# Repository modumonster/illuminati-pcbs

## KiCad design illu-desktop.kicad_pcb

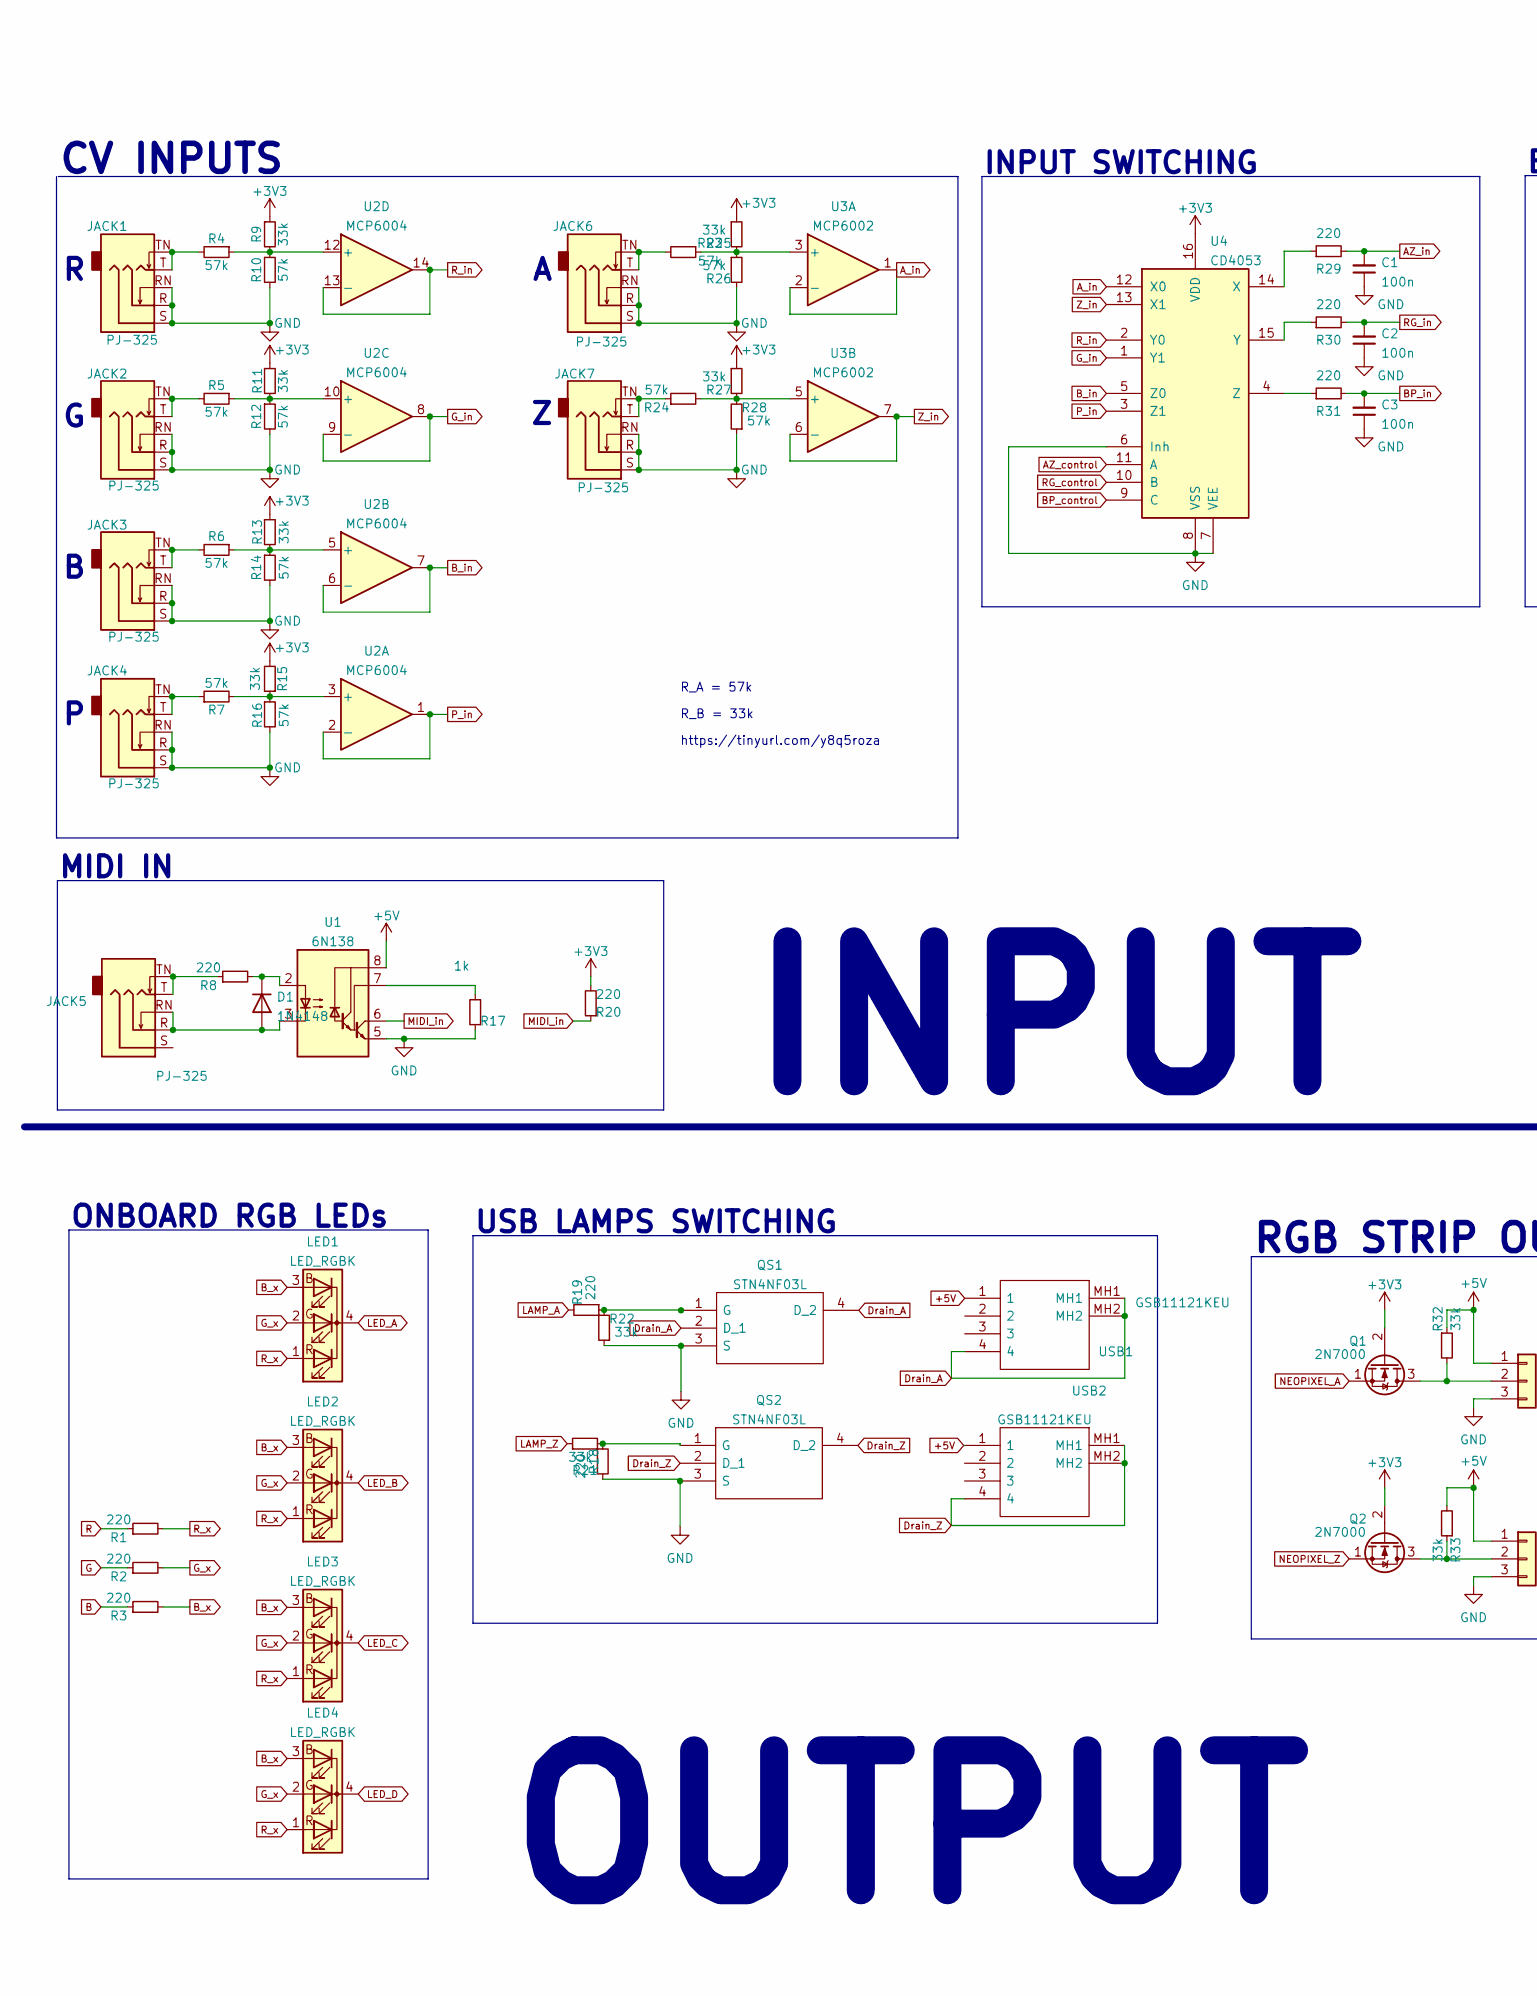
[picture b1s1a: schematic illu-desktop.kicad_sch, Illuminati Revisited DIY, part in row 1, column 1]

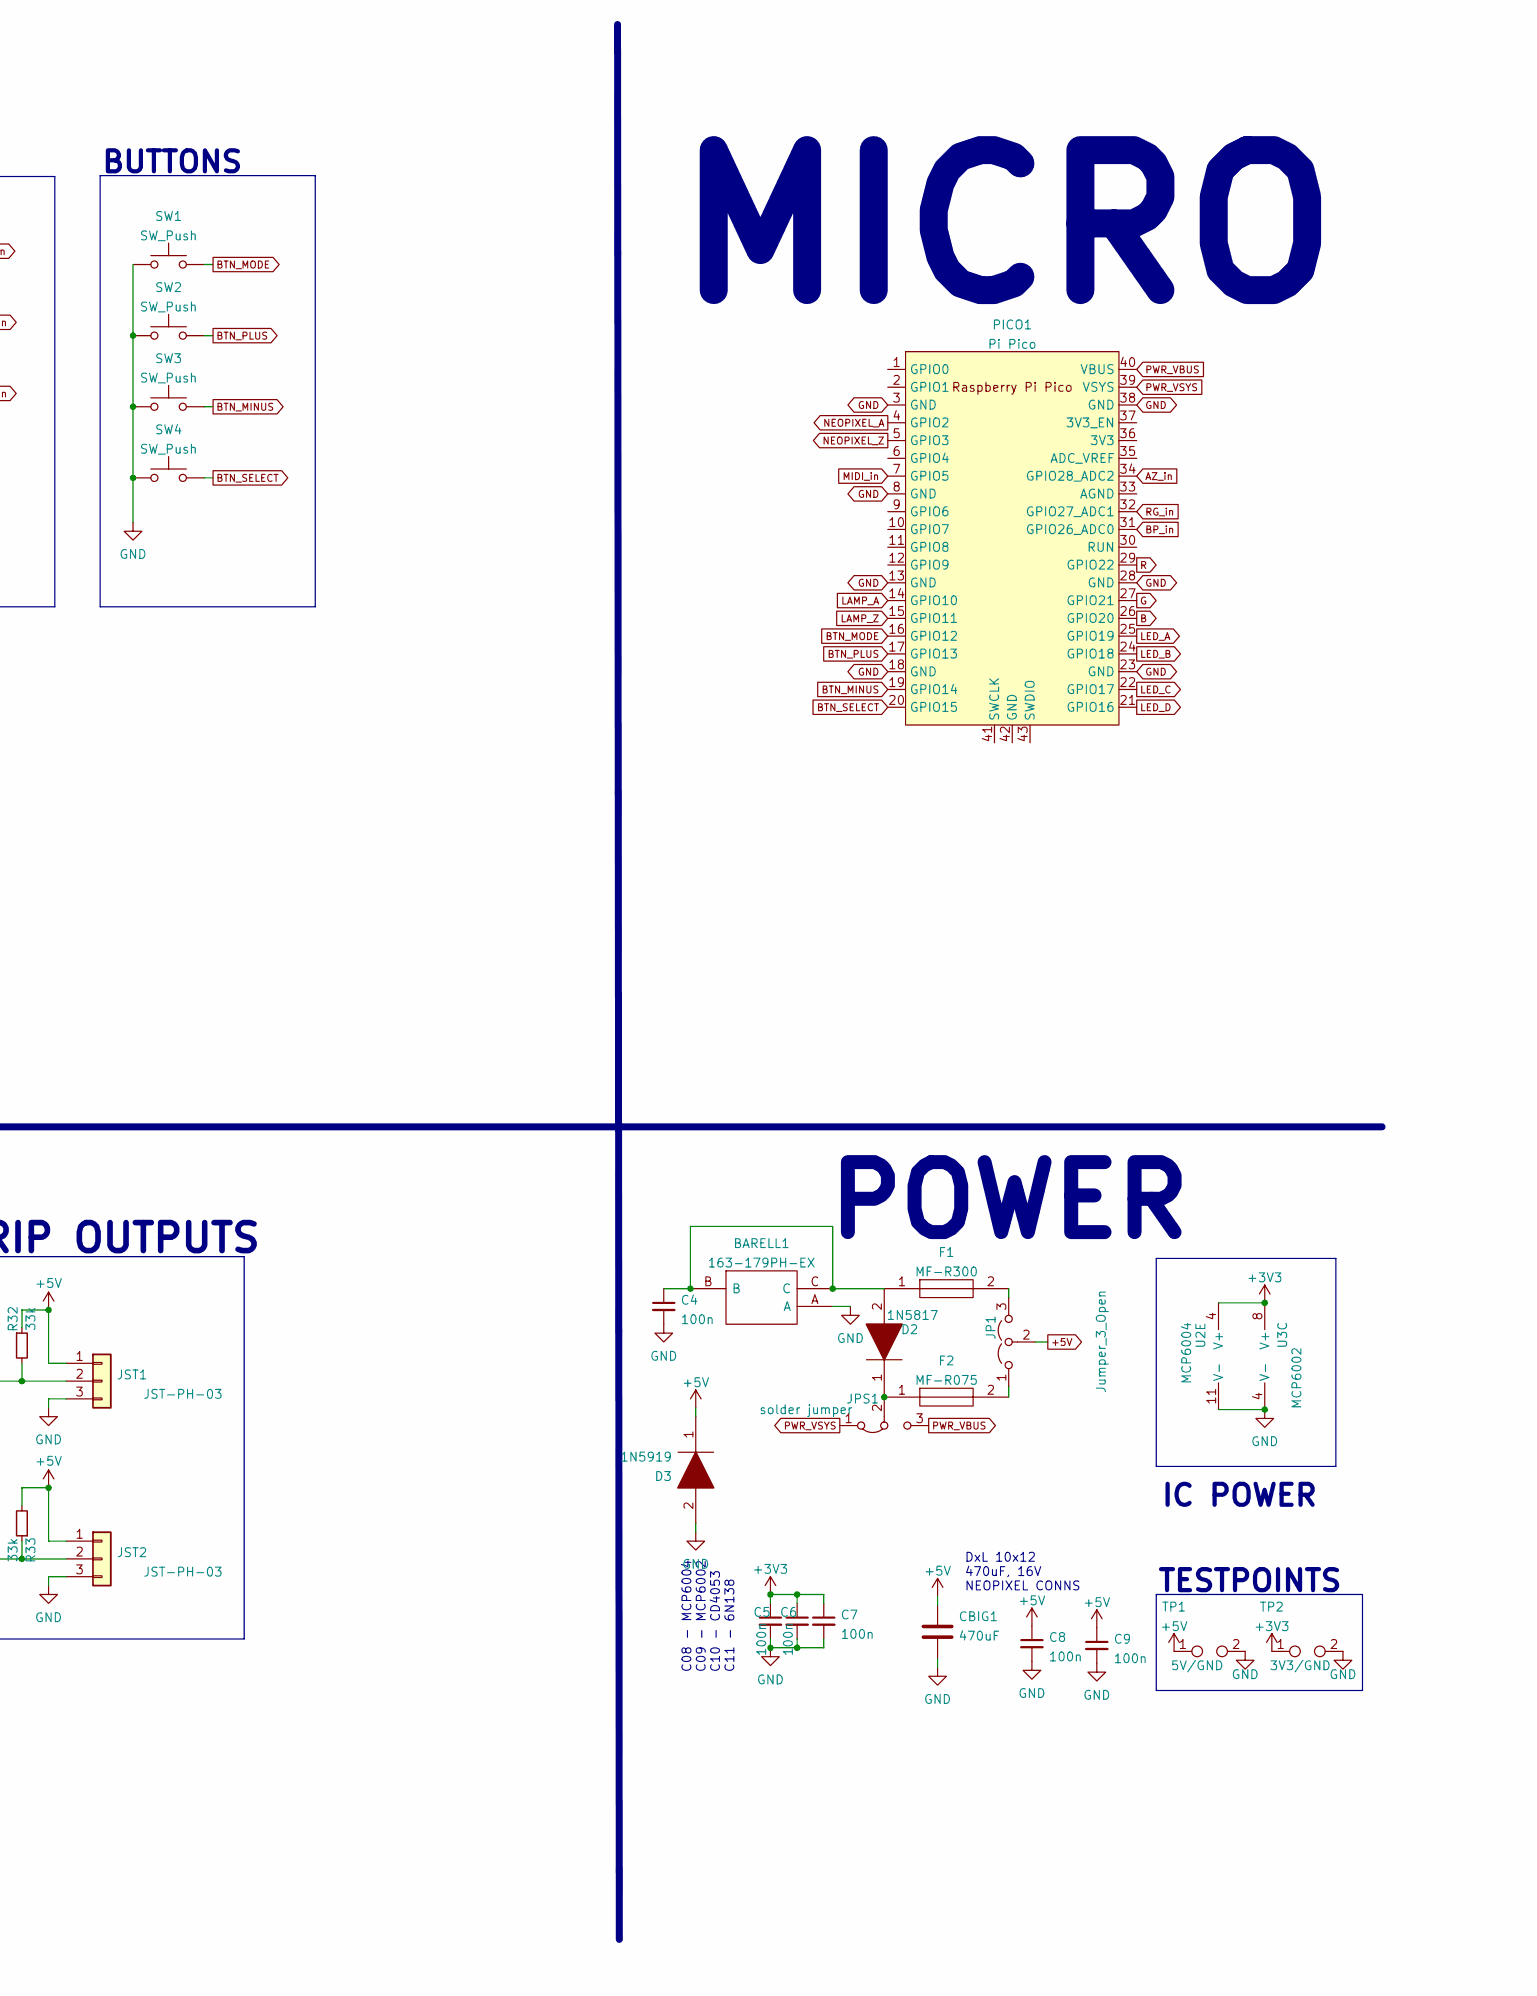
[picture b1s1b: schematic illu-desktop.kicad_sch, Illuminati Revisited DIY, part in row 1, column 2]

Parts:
BARELL1: 163-179PH-EX; BarellJack; Mouser Part Number 163-179PH-EX
C1, C2, C3, C4, C5, C6, C7, C8, C9: 100n; C_Rect_L7.0mm_W2.5mm_P5.00mm
CBIG1: 470uF; CP_Radial_D10.0mm_P5.00mm
D1: 1N4148; D_DO-35_SOD27_P7.62mm_Horizontal
D2: 1N5817; D_DO-41_SOD81_P7.62mm_Horizontal; Mouser Part Number 863-1N5817RLG
D3: 1N5919; D_DO-41_SOD81_P7.62mm_Horizontal; Mouser Part Number 863-1N5919BG
F1: MF-R300; MFR300; Mouser Part Number 652-MFR300
F2: MF-R075; MFR075; Mouser Part Number 652-MFR075
JACK1, JACK2, JACK3, JACK4, JACK5, JACK6, JACK7: PJ-325; PJ-325C5
JP1: Jumper_3_Open; PinHeader_1x03_P2.54mm_Horizontal
JPS1: solder jumper; SolderJumper-3_P1.3mm_Bridged12_RoundedPad1.0x1.5mm
JST1, JST2: JST-PH-03; JST_PH_S3B-PH-K_1x03_P2.00mm_Horizontal
LED1, LED2, LED3, LED4: LED_RGBK; LED_D5.0mm-4_RGB
PICO1: Pi Pico; RPi_Pico_TH
Q1, Q2: 2N7000; TO-92_Inline
QS1, QS2: STN4NF03L; SOT233P700X180-4N; Mouser Part Number 511-STN4NF03L
R1, R2, R3: 220; R_Axial_DIN0207_L6.3mm_D2.5mm_P7.62mm_Horizontal
R4, R5, R6, R7, R10, R12, R14, R16, R23, R24, R26, R28: 57k; R_Axial_DIN0207_L6.3mm_D2.5mm_P2.54mm_Vertical
R8, R18, R19, R20, R29, R30, R31: 220; R_Axial_DIN0207_L6.3mm_D2.5mm_P2.54mm_Vertical
R9, R11, R13, R15, R21, R22, R25, R27, R32, R33: 33k; R_Axial_DIN0207_L6.3mm_D2.5mm_P2.54mm_Vertical
R17: 1k; R_Axial_DIN0207_L6.3mm_D2.5mm_P2.54mm_Vertical
SW1, SW2, SW3, SW4: SW_Push; SW_PUSH_6mm_H17mm
TP1: 5V/GND; TestPoint_2Pads_Pitch2.54mm_Drill0.8mm
TP2: 3V3/GND; TestPoint_2Pads_Pitch2.54mm_Drill0.8mm
U1: 6N138; DIP-8_W7.62mm
U2: MCP6004; DIP-14_W7.62mm
U3: MCP6002; DIP-8_W7.62mm
U4: CD4053; DIP-16_W7.62mm
USB1, USB2: GSB11121KEU; Mouser Part Number 523-GSB11121KEU

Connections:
+3V3: C5.1, C6.1, C7.1, Q1.2 (G), Q2.2 (G), R9.1, R11.1, R13.1, R15.2, R20.2, R25.1, R27.1, TP2.1, U2.4 (V+), U3.8 (V+), U4.16 (VDD)
+5V: C8.1, C9.1, CBIG1.1, D3.1, JP1.2 (C), JST1.1, JST2.1, R32.1, R33.2, TP1.1, U1.8 (VCC), USB1.1, USB2.1
AZ_control: U4.11 (A)
AZ_in: C1.2, PICO1.34 (GPIO28_ADC2), R29.2
A_in: U3.1, U3.2 (-), U4.12 (X0)
B: PICO1.26 (GPIO20), R3.1
BP_control: U4.9 (C)
BP_in: C3.2, PICO1.31 (GPIO26_ADC0), R31.2
BTN_MINUS: PICO1.19 (GPIO14), SW3.2
BTN_MODE: PICO1.16 (GPIO12), SW1.2
BTN_PLUS: PICO1.17 (GPIO13), SW2.2
BTN_SELECT: PICO1.20 (GPIO15), SW4.2
B_in: U2.6 (-), U2.7, U4.5 (Z0)
B_x: LED1.3 (BA), LED2.3 (BA), LED3.3 (BA), LED4.3 (BA), R3.2
Drain_A: QS1.2 (D_1), QS1.4 (D_2), USB1.4, USB1.MH1, USB1.MH2
Drain_Z: QS2.2 (D_1), QS2.4 (D_2), USB2.4, USB2.MH1, USB2.MH2
G: PICO1.27 (GPIO21), R2.1
GND: BARELL1.A, C1.1, C2.1, C3.1, C4.2, C5.2, C6.2, C7.2, C8.2, C9.2, CBIG1.2, D3.2, JACK1.R, JACK1.RN, JACK1.S, JACK2.R, JACK2.RN, JACK2.S, JACK3.R, JACK3.RN, JACK3.S, JACK4.R, JACK4.RN, JACK4.S, JACK6.R, JACK6.RN, JACK6.S, JACK7.R, JACK7.RN, JACK7.S, JST1.3, JST2.3, PICO1.3 (GND), PICO1.8 (GND), PICO1.13 (GND), PICO1.18 (GND), PICO1.23 (GND), PICO1.28 (GND), PICO1.38 (GND), QS1.3 (S), QS2.3 (S), R10.2, R12.2, R14.2, R16.2, R17.1, R21.2, R22.1, R26.2, R28.1, SW1.1, SW2.1, SW3.1, SW4.1, TP1.2, TP2.2, U1.5 (GND), U2.11 (V-), U3.4 (V-), U4.6 (Inh), U4.7 (VEE), U4.8 (VSS)
G_in: U2.8, U2.9 (-), U4.1 (Y1)
G_x: LED1.2 (GA), LED2.2 (GA), LED3.2 (GA), LED4.2 (GA), R2.2
LAMP_A: PICO1.14 (GPIO10), R19.2
LAMP_Z: PICO1.15 (GPIO11), R18.1
LED_A: LED1.4 (K), PICO1.25 (GPIO19)
LED_B: LED2.4 (K), PICO1.24 (GPIO18)
LED_C: LED3.4 (K), PICO1.22 (GPIO17)
LED_D: LED4.4 (K), PICO1.21 (GPIO16)
MIDI_in: PICO1.7 (GPIO5), R20.1, U1.6 (VO2)
NEOPIXEL_A: PICO1.4 (GPIO2), Q1.1 (S)
NEOPIXEL_Z: PICO1.5 (GPIO3), Q2.1 (S)
unnamed: BARELL1.B, BARELL1.C, C4.1, D2.2, F1.1
unnamed: D1.1 (K), R8.2, U1.2 (C1)
unnamed: D1.2 (A), JACK5.R, JACK5.RN, U1.3 (C2)
unnamed: D2.1, F2.1, JPS1.2 (C)
unnamed: F1.2, JP1.3 (B)
unnamed: F2.2, JP1.1 (A)
unnamed: JACK1.T, JACK1.TN, R4.2
unnamed: JACK2.T, JACK2.TN, R5.2
unnamed: JACK3.T, JACK3.TN, R6.2
unnamed: JACK4.T, JACK4.TN, R7.1
unnamed: JACK5.T, JACK5.TN, R8.1
unnamed: JACK6.T, JACK6.TN, R23.2
unnamed: JACK7.T, JACK7.TN, R24.1
unnamed: JST1.2, Q1.3 (D), R32.2
unnamed: JST2.2, Q2.3 (D), R33.1
unnamed: QS1.1 (G), R19.1, R22.2
unnamed: QS2.1 (G), R18.2, R21.1
unnamed: R4.1, R9.2, R10.1, U2.12 (+)
unnamed: R5.1, R11.2, R12.1, U2.10 (+)
unnamed: R6.1, R13.2, R14.1, U2.5 (+)
unnamed: R7.2, R15.1, R16.1, U2.3 (+)
unnamed: R17.2, U1.7 (VO1)
unnamed: R23.1, R25.2, R26.1, U3.3 (+)
unnamed: R24.2, R27.2, R28.2, U3.5 (+)
unnamed: R29.1, U4.14 (X)
unnamed: R30.1, U4.15 (Y)
unnamed: R31.1, U4.4 (Z)
PWR_VBUS: JPS1.3 (B), PICO1.40 (VBUS)
PWR_VSYS: JPS1.1 (A), PICO1.39 (VSYS)
P_in: U2.1, U2.2 (-), U4.3 (Z1)
R: PICO1.29 (GPIO22), R1.1
RG_control: U4.10 (B)
RG_in: C2.2, PICO1.32 (GPIO27_ADC1), R30.2
R_in: U2.13 (-), U2.14, U4.2 (Y0)
R_x: LED1.1 (RA), LED2.1 (RA), LED3.1 (RA), LED4.1 (RA), R1.2
Z_in: U3.6 (-), U3.7, U4.13 (X1)

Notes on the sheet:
DxL 10x12 470uF, 16V NEOPIXEL CONNS
BUTTONS
https://tinyurl.com/y8q5roza
INPUT SWITCHING
OUTPUT
R_B = 33k
CV INPUTS
POWER
MIDI IN
INPUT
TESTPOINTS
MICRO
C08 - MCP6004 C09 - MCP6002 C10 - CD4053 C11 - 6N138
IC POWER
USB LAMPS SWITCHING
ONBOARD RGB LEDs
RGB STRIP OUTPUTS
R_A = 57k

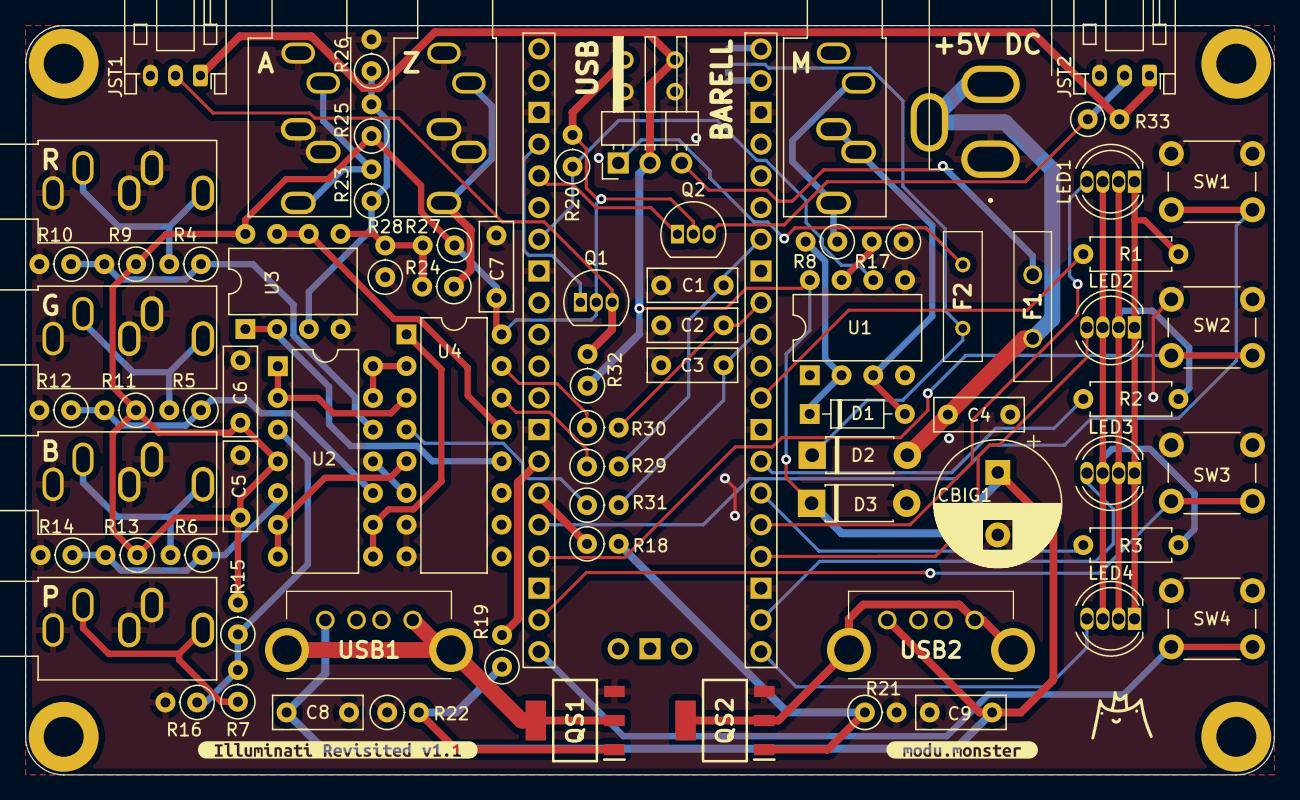
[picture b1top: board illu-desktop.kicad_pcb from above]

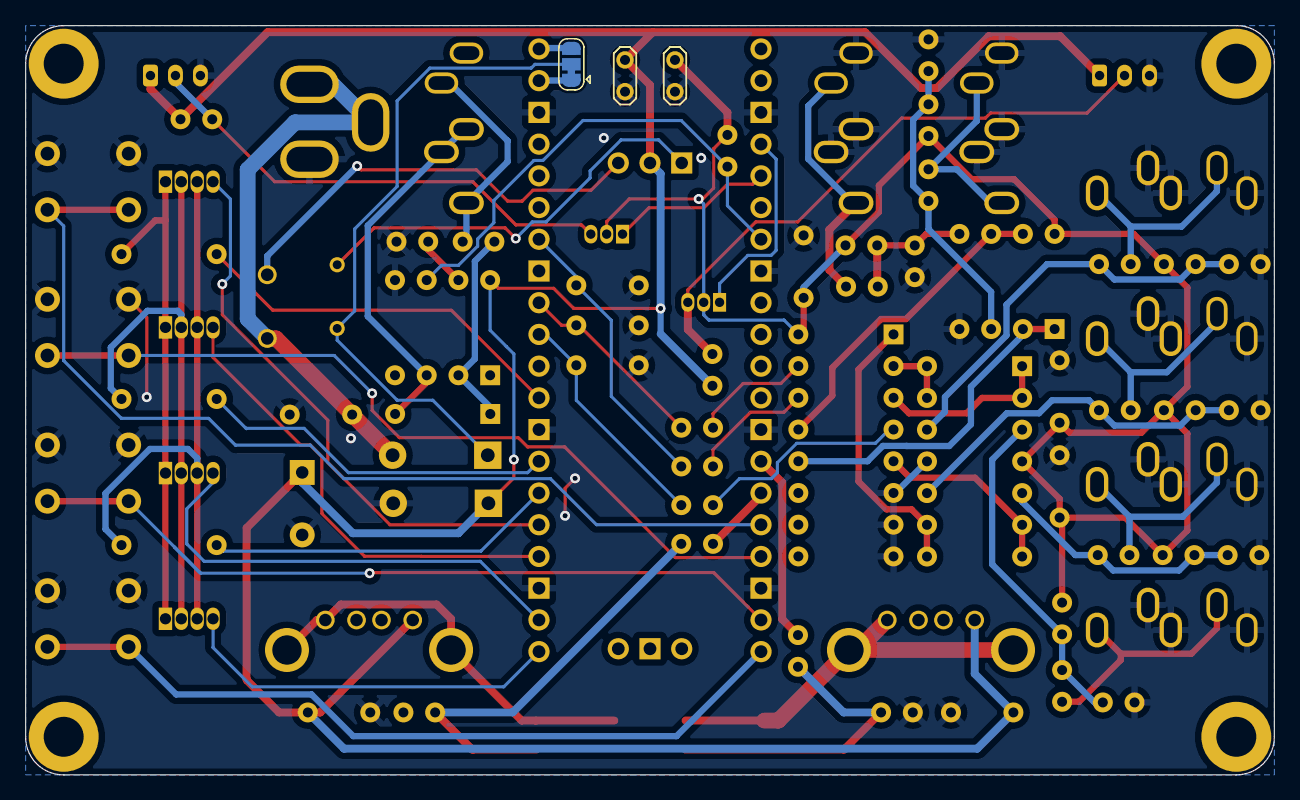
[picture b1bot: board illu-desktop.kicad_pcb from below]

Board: 2 copper layers, 100.0 x 60.0 mm, 83 parts (3 on the bottom side), 62 nets.

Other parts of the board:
kibuzzard-622E32B3: G***; kibuzzard-622E32B3
kibuzzard-622E327E: G***; kibuzzard-622E327E

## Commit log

2022-06-03 Just commited, please dont roast me
